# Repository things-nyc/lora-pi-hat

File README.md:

# lora-pi-hat
Raspberry Pi HAT for mPCIe LoRa gateway cards

Untested
* jumpers are probably unnecessary because SPI pins are independent
* u-blox module can be swapped for *much* cheaper alternative
* gateway current consumption @3.3V ~ 500mA, DC/DC designed for 1A

| Pin | mini PCIe  | MTAC        | RAK      |
|-----|------------|-------------|----------|
| 1   | WAKE#      |             |          |
| 2   | 3.3Vaux    | VDD_3V3     | VDD_3V3  |
| 3   | COEX1      |             |          |
| 4   | GND        | GND         | GND      |
| 5   | COEX2      | SPI_MOSI    |          |
| 6   | 1.5Vaux    |             |          |
| 7   | CLKREQ#    | SPI_MISO    |          |
| 8   | UIM_PWR    |             |          |
| 9   | GND        | GND         | GND      |
| 10  | UIM_DATA   |             |          |
| 11  | REFCLK-    |             |          |
| 12  | UIM_CLK    | SPI_NCS     |          |
| 13  | REFCLK+    | SPI_CLK     |          |
| 14  | UIM_RESET  | ?           |          |
| 15  | GND        | GND         | GND      |
| 16  | UIM_VPP    |             |          |
| 17  | Reserved   |             |          |
| 18  | GND        | GND         | GND      |
| 19  | Reserved   |             | GPS_PPS  |
| 20  | W_DISABLE# |             |          |
| 21  | GND        | GND         | GND      |
| 22  | PERST#     | RESET       | RESET    |
| 23  | PERn0      | VDD_5V      |          |
| 24  | 3.3Vaux    | VDD_3V3     | VDD_3V3  |
| 25  | PERp0      | VDD_5V      |          |
| 26  | GND        | GND         | GND      |
| 27  | GND        | EEPROM_A1   | GND      |
| 28  | 1.5Vaux    | GPS_PPS     |          |
| 29  | GND        | EEPROM_A2   | GND      |
| 30  | SMB_CLK    | I2C_SCL     |          |
| 31  | PETn0      |             |          |
| 32  | SMB_DATA   | I2C_SDA     |          |
| 33  | PETp0      |             |          |
| 34  | GND        | GND         | GND      |
| 35  | GND        | GND         | GND      |
| 36  | USB_D-     |             |          |
| 37  | GND        | GND         | GND      |
| 38  | USB_D+     |             |          |
| 39  | 3.3Vaux    | VDD_3V3     | VDD_3V3  |
| 40  | GND        | GND         | GND      |
| 41  | 3.3Vaux    | VDD_3V3     | VDD_3V3  |
| 42  | LED_WWAN#  | ?           |          |
| 43  | GND        | GND         | GND      |
| 44  | LED_WLAN#  |             |          |
| 45  | Reserved   |             | SPI_CLK  |
| 46  | LED_WPAN#  |             |          |
| 47  | Reserved   |             | SPI_MISO |
| 48  | 1.5Vaux    |             |          |
| 49  | Reserved   |             | SPI_MOSI |
| 50  | GND        | GND         | GND      |
| 51  | Reserved   |             | SPI_NCS  |
| 52  | 3.3Vaux    | VDD_3V3     | VDD_3V3  |

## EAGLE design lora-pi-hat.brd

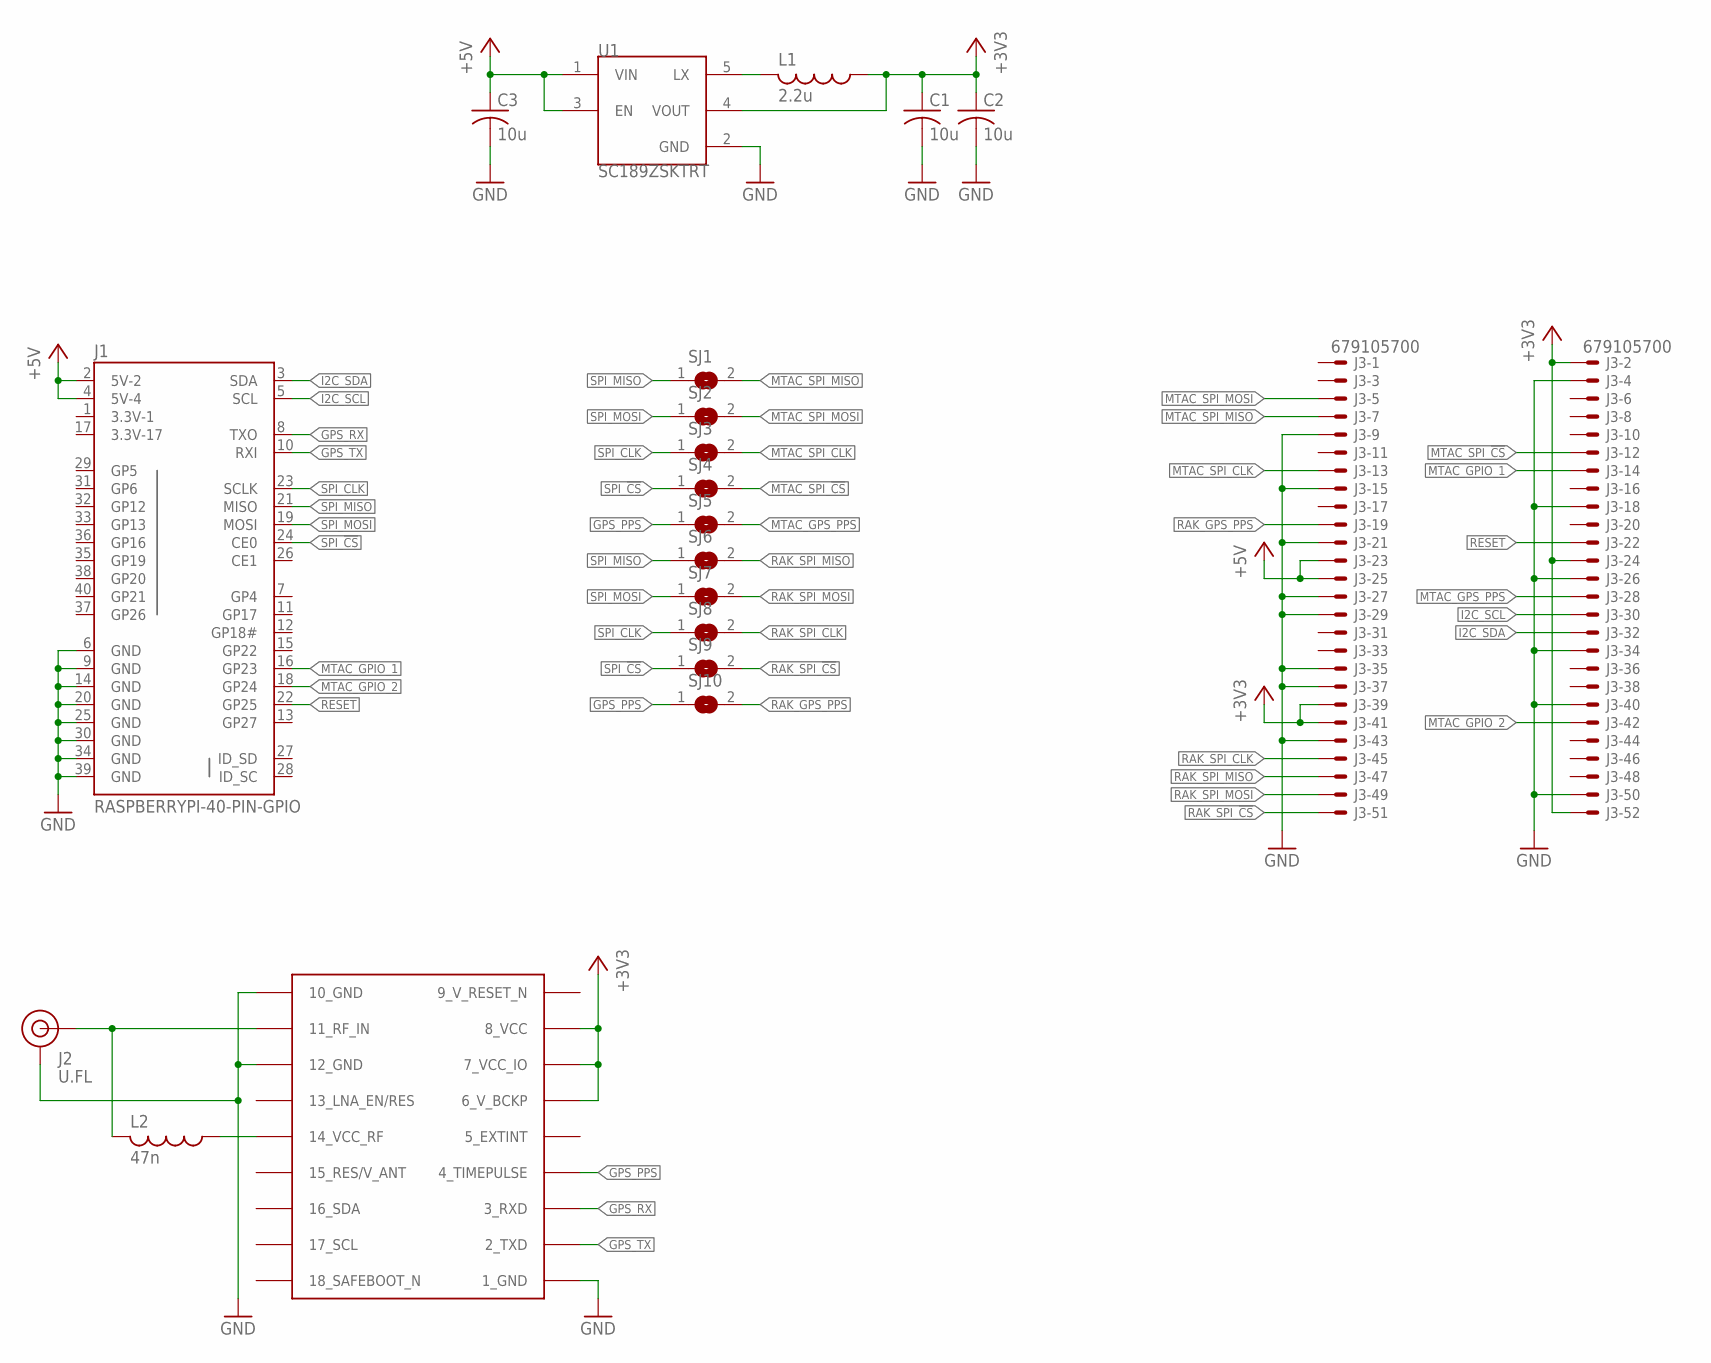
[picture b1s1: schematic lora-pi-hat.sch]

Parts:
C1, C2, C3: 10u; CAPC2012X125N
J1: RASPBERRYPI-40-PIN-GPIO; 2X20
J2: U.FL
J3: 679105700
L1: 2.2u; INDC3225X250N
L2: 47n; INDC2012X125N
SJ1, SJ2, SJ3, SJ4, SJ5, SJ6, SJ7, SJ8, SJ9, SJ10: SJ
U1: SC189ZSKTRT; SOT95P280X120-5N
U2: MAX-M8

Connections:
3.3V-1: J1.1 (3.3V-1)
3.3V-17: J1.17 (3.3V-17)
9_V_RESET_N: U2.9_RESET_N (9_V_RESET_N)
+3V3: C1.1, C2.1, J3.2, J3.24, J3.39, J3.41, J3.52, L1.1, U1.4 (VOUT), U2.6_V_BCKP, U2.7_VCC_IO, U2.8_VCC
+5V: C3.1, J1.2 (5V-2), J1.4 (5V-4), J3.23, J3.25, U1.1 (VIN), U1.3 (EN)
GND: C1.2, C2.2, C3.2, J1.6 (GND), J1.9 (GND), J1.14 (GND), J1.20 (GND), J1.25 (GND), J1.30 (GND), J1.34 (GND), J1.39 (GND), J2.1 (GND), J2.2 (GND), J3.4, J3.9, J3.15, J3.18, J3.21, J3.26, J3.27, J3.29, J3.34, J3.35, J3.37, J3.40, J3.43, J3.50, U1.2 (GND), U2.1_GND, U2.10_GND, U2.12_GND
GPS_PPS: SJ5.1, SJ10.1, U2.4_TIMEPULSE
GPS_RX: J1.8 (TXO), U2.3_RXD
GPS_TX: J1.10 (RXI), U2.2_TXD
I2C_SCL: J1.5 (SCL), J3.30
I2C_SDA: J1.3 (SDA), J3.32
MTAC_GPIO_1: J1.16 (GP23), J3.14
MTAC_GPIO_2: J1.18 (GP24), J3.42
MTAC_GPS_PPS: J3.28, SJ5.2
MTAC_SPI_!CS: J3.12, SJ4.2
MTAC_SPI_CLK: J3.13, SJ3.2
MTAC_SPI_MISO: J3.7, SJ1.2
MTAC_SPI_MOSI: J3.5, SJ2.2
unnamed: L1.2, U1.5 (LX)
unnamed: L2.1, U2.14_VCC_RF
unnamed: J2.FEED (SIGNAL), L2.2, U2.11_RF_IN
RAK_GPS_PPS: J3.19, SJ10.2
RAK_SPI_!CS: J3.51, SJ9.2
RAK_SPI_CLK: J3.45, SJ8.2
RAK_SPI_MISO: J3.47, SJ6.2
RAK_SPI_MOSI: J3.49, SJ7.2
RESET: J1.22 (GP25), J3.22
SPI_!CS: J1.24 (CE0), SJ4.1, SJ9.1
SPI_CLK: J1.23 (SCLK), SJ3.1, SJ8.1
SPI_MISO: J1.21 (MISO), SJ1.1, SJ6.1
SPI_MOSI: J1.19 (MOSI), SJ2.1, SJ7.1

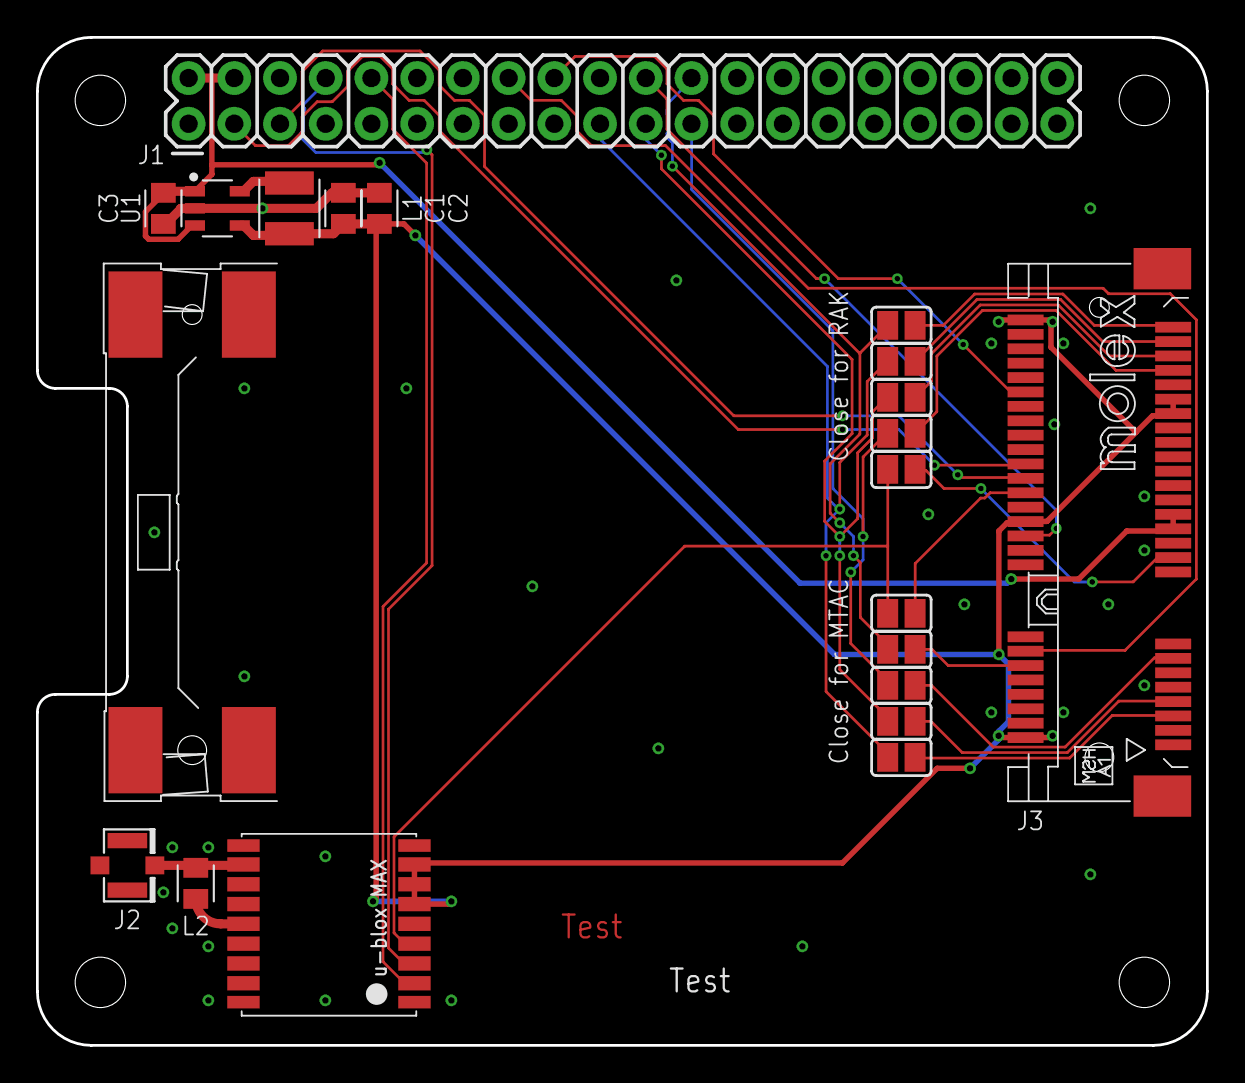
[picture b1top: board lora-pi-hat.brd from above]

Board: 2 copper layers, 65.0 x 56.0 mm, 20 parts (0 on the bottom side), 28 nets.

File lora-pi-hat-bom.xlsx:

Qty | Parts | Value | Device | Package | Digikey PN | Description | Notes
3 | C1, C2, C3 | 10u | C-US-0805 | CAPC2012X125N | 587-1300-1-ND | Capacitor
1 | L1 | 2.2u | L-US-1210 | INDC3225X250N | 587-2427-1-ND | Buck Inductor
1 | L2 | 47n | L-US-0805 | INDC2012X125N | 2035-1277-1-ND | Bias Inductor
1 | J3 | 679105700 | 679105700 | 679105700 | WM3471CT-ND | MOLEX MINI PCI EXPRESS CONNECTOR
1 |  |  |  |  | WM3294CT-ND | MOLEX MINI PCI EXPRESS LATCH
1 | U2 | MAX-M8 | MAX-M8 | MAX-M8 | 672-MAX-M8W-0-10CT-ND | u-blox MAX GNSS module | Save $ with ATGM336H from LCSC
1 | J1 | RASPBERRYPI-40-PIN-GPIO | RASPBERRYPI-40-PIN-GPIO | 2X20 | S6104-ND | Raspberry Pi GPIO Header
1 | U1 | SC189ZSKTRT | SC189ZSKTRT | SOT95P280X120-5N | SC189ZSKCT-ND | Buck Regulator
1 | J2 | U.FL | U.FL2PIN | U.FL | A118077CT-ND | SMD Antenna Connector - U.FL

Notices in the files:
parts and their libraries:
SparkFun-Connectors: Licensing: Creative Commons ShareAlike 4.0 International - https://creativecommons.org/licenses/by-sa/4.0
